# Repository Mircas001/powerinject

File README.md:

# powerinject
Combine the power from your charger with the data lines from your PC into one USB-C output!

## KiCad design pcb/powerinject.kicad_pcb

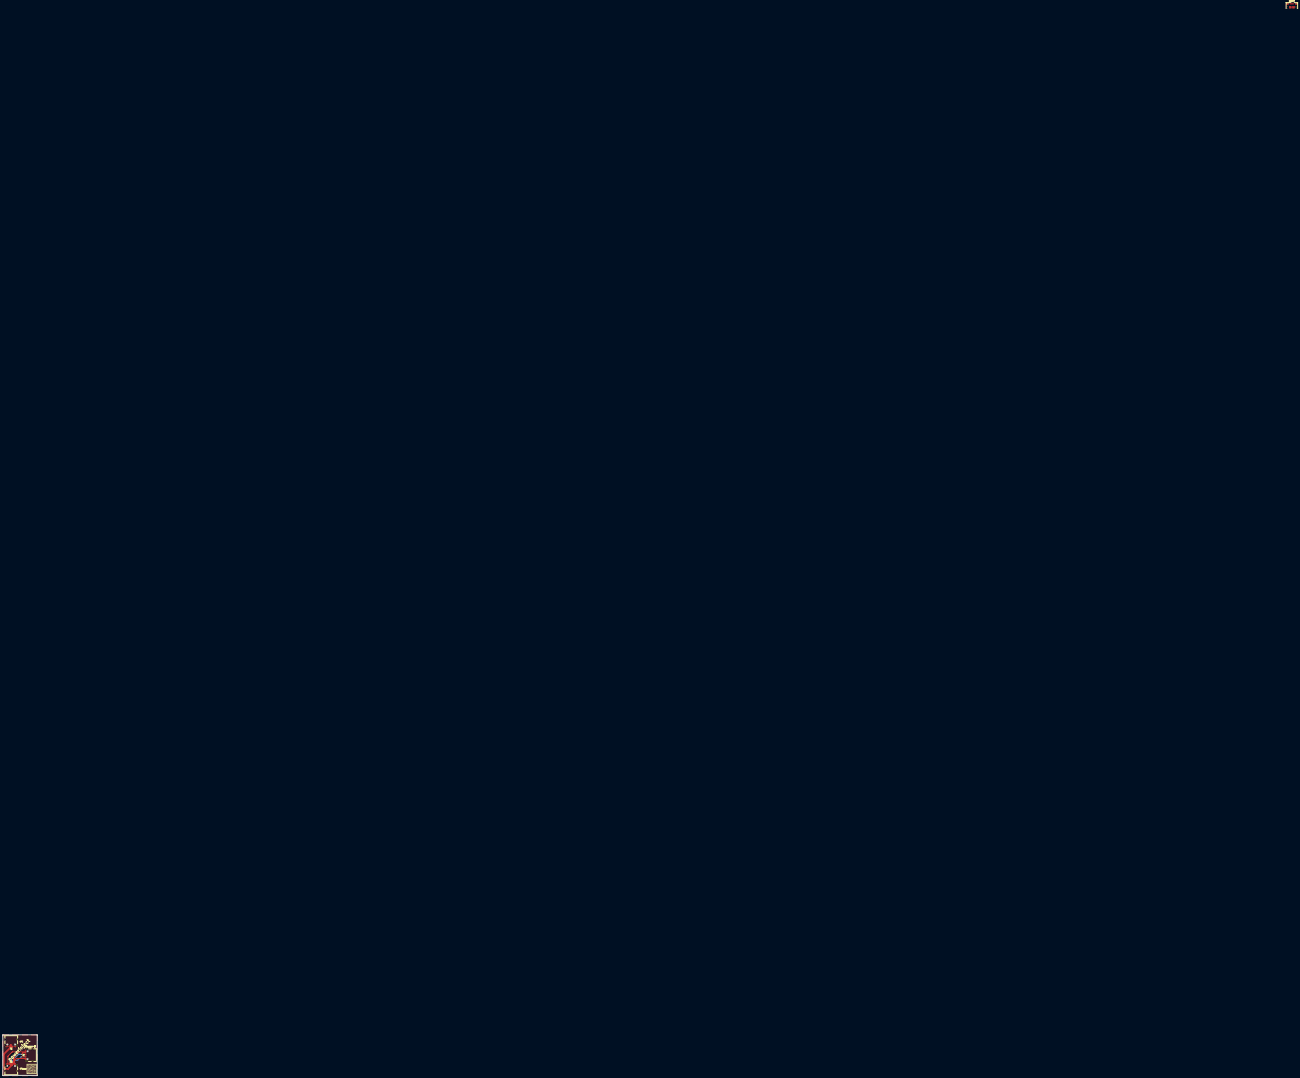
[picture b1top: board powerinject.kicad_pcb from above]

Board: 2 copper layers, 25.5 x 30.0 mm, 3 parts (0 on the bottom side), 6 nets.

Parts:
J1: PC_Usb; USB_C_Receptacle_HRO_TYPE-C-31-M-12
J2: Charger_USB; USB_C_Receptacle_HRO_TYPE-C-31-M-12
J3: Phone_USB; USB_C_Receptacle_HRO_TYPE-C-31-M-12

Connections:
GND: J1.A1 (GND), J1.A12 (GND), J1.B1 (GND), J1.B12 (GND), J1.SH (SHIELD), J2.A1 (GND), J2.A12 (GND), J2.B1 (GND), J2.B12 (GND), J2.SH (SHIELD), J3.A1 (GND), J3.A12 (GND), J3.B1 (GND), J3.B12 (GND), J3.SH (SHIELD)
unnamed: J1.A6 (D+), J1.B6 (D+), J3.A6 (D+), J3.B6 (D+)
unnamed: J1.A7 (D-), J1.B7 (D-), J3.A7 (D-), J3.B7 (D-)
unnamed: J2.A5 (CC1), J3.A5 (CC1)
unnamed: J2.B5 (CC2), J3.B5 (CC2)
VBUS: J2.A4 (VBUS), J2.A9 (VBUS), J2.B4 (VBUS), J2.B9 (VBUS), J3.A4 (VBUS), J3.A9 (VBUS), J3.B4 (VBUS), J3.B9 (VBUS)

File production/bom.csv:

Designator,Footprint,Quantity,Value,LCSC Part #
J1,USB_C_Receptacle_HRO_TYPE-C-31-M-12,1,PC_Usb,
J2,USB_C_Receptacle_HRO_TYPE-C-31-M-12,1,Charger_USB,
J3,USB_C_Receptacle_HRO_TYPE-C-31-M-12,1,Phone_USB,
